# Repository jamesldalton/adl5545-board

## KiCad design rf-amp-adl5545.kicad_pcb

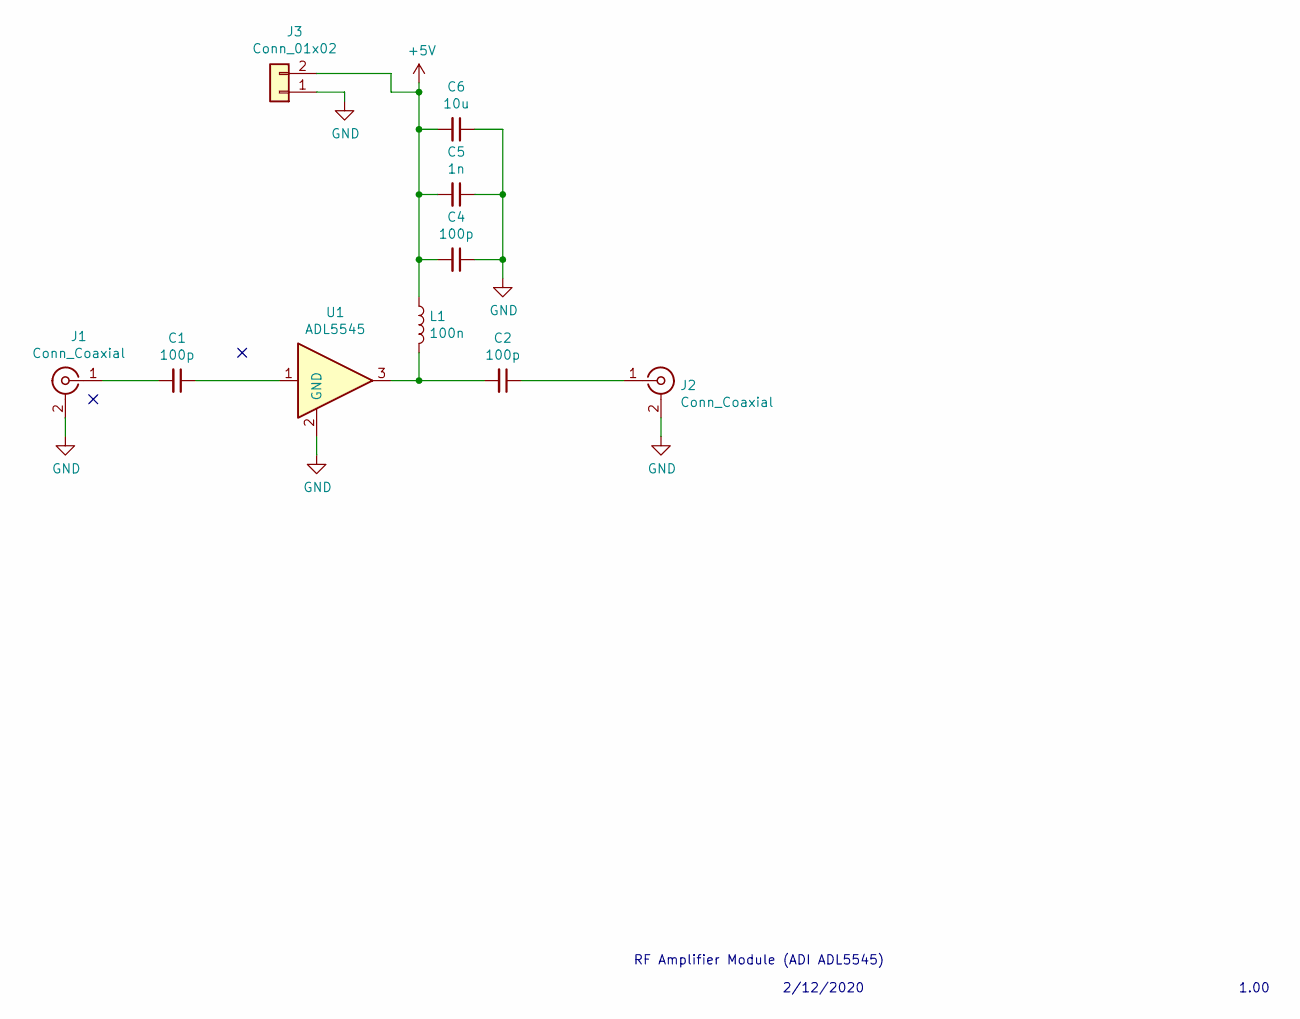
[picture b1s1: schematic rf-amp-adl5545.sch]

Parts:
C1, C2, C4: 100p; C_0603_1608Metric_Pad1.05x0.95mm_HandSolder
C5: 1n; C_0603_1608Metric_Pad1.05x0.95mm_HandSolder
C6: 10u; C_1206_3216Metric_Pad1.42x1.75mm_HandSolder
J1, J2: Conn_Coaxial; SMA_Amphenol_132289_EdgeMount
J3: Conn_01x02; PinHeader_1x02_P2.54mm_Vertical
L1: 100n; L_0603_1608Metric_Pad1.05x0.95mm_HandSolder
U1: ADL5545; SOT-89-3_Handsoldering

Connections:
+5V: C4.2, C5.2, C6.2, J3.2, L1.1
GND: C4.1, C5.1, C6.1, J1.2 (Ext), J2.2 (Ext), J3.1, U1.2 (GND)
unnamed: C1.1, U1.1
unnamed: C1.2, J1.1 (In)
unnamed: C2.1, J2.1 (In)
unnamed: C2.2, L1.2, U1.3

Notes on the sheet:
RF Amplifier Module (ADI ADL5545)
1.00
2/12/2020

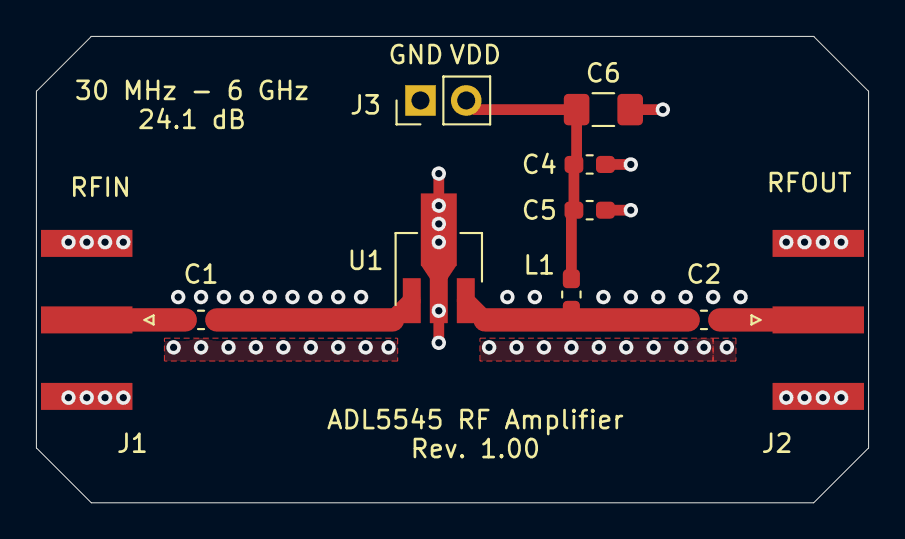
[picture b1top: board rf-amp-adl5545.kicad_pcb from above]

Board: 2 copper layers, 46.2 x 25.9 mm, 10 parts (0 on the bottom side), 6 nets.

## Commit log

2020-03-04 uploading finished board
